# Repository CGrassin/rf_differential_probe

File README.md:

# RF Passive Differential Probe

Article about the project: https://charleslabs.fr/en/project-RF+Passive+Differential+Probe

This passive RF differential probe is a cost-effective solution for in-circuit measurements of RF systems operating within the frequency range of 500 MHz to 6 GHz. It is well-suited for situations where a test port is unavailable and it is engineered to have minimal impact on the device under test.

The probe's spring-loaded pins can be positioned at any angle to fit the ground-signal track spacing, with a practical lower bound of 1 mm, equivalent to the length of an 0402 component.

Compared to commercial active probes, this probe is significantly more affordable and has a different input power range, making it suitable for use on high-power RF circuits for instance.

A typical application for this probe is for tuning multiple-stage RF power amplifiers.

This repository contains the KiCad files (schmematic and PCB layout).

## License

This probe is licensed under the BSD 4-clause license, please see the LICENSE file.

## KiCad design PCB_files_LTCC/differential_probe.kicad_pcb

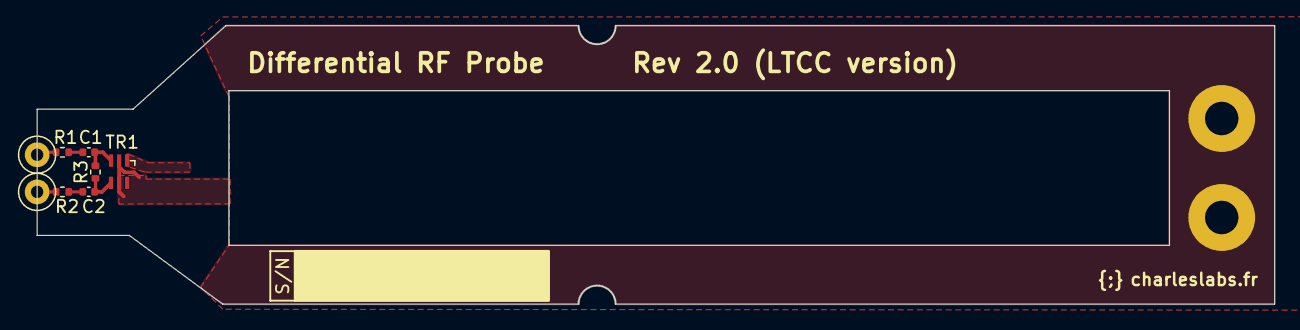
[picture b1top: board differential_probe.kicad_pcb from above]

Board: 2 copper layers, 100.0 x 22.5 mm, 10 parts (0 on the bottom side), 8 nets.

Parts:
C1, C2: 1p,N0G; C_0402_1005Metric
H1, H2: MountingHole_Pad; MountingHole_2.7mm_M2.5_Pad
R1, R2: 220; R_0402_1005Metric
R3: DNP; R_0402_1005Metric
TP1, TP2: Pogo pin; TestPoint_Loop_D1.80mm_Drill1.0mm_Beaded
TR1: NCS1-332+; Mini-Circuits_GE0805C-x

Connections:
/RF_GND: TR1.2, TR1.5
GND: H1.1 (1_1), H2.1 (1_1)
unnamed: C1.1, R1.2
unnamed: C1.2, R3.2, TR1.3
unnamed: C2.1, R2.2
unnamed: C2.2, R3.1, TR1.4
unnamed: R1.1, TP1.1 (1_1)
unnamed: R2.1, TP2.1 (1_1)

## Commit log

2023-04-07 Added simulation files (QucsStudio)
2023-04-07 Fixed R2 resistor value
2023-04-07 Added alternative part number note
2023-04-07 Initial rev.2 commit: swapped R and C location, lengthen probe by 25 mm (one ferrite), shortened TP to R distance
2023-04-07 Changed project structure, added symbol lib
2023-04-07 Fixed NCS1-332+ symbol
2023-04-07 Fixed symbol and footprint library for transformers
2023-04-07 Shortened RF path, fixed silkscreen
2026-05-14 Update files for manufacturing
2026-05-14 Simulation files cleanup
2026-05-15 Updated simulation model for rev. 2
